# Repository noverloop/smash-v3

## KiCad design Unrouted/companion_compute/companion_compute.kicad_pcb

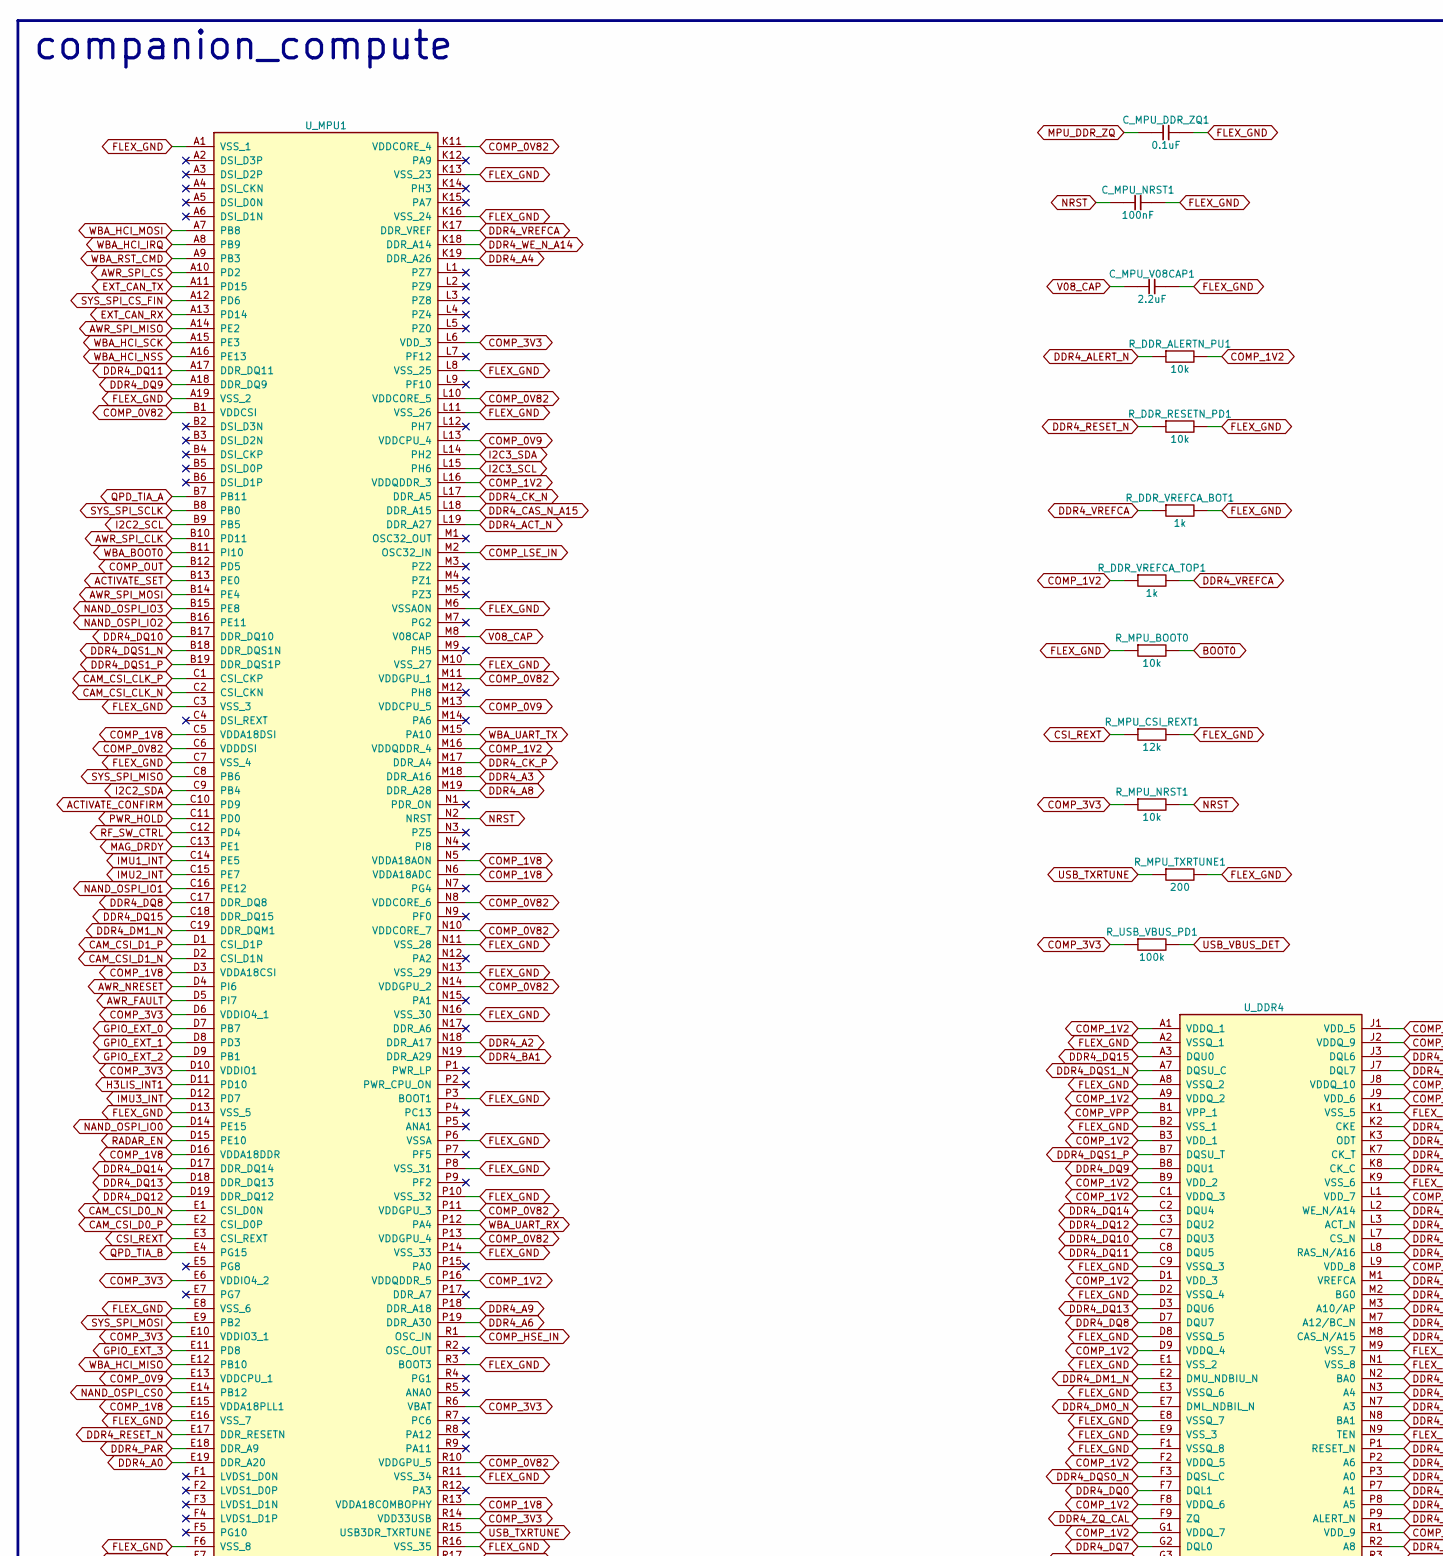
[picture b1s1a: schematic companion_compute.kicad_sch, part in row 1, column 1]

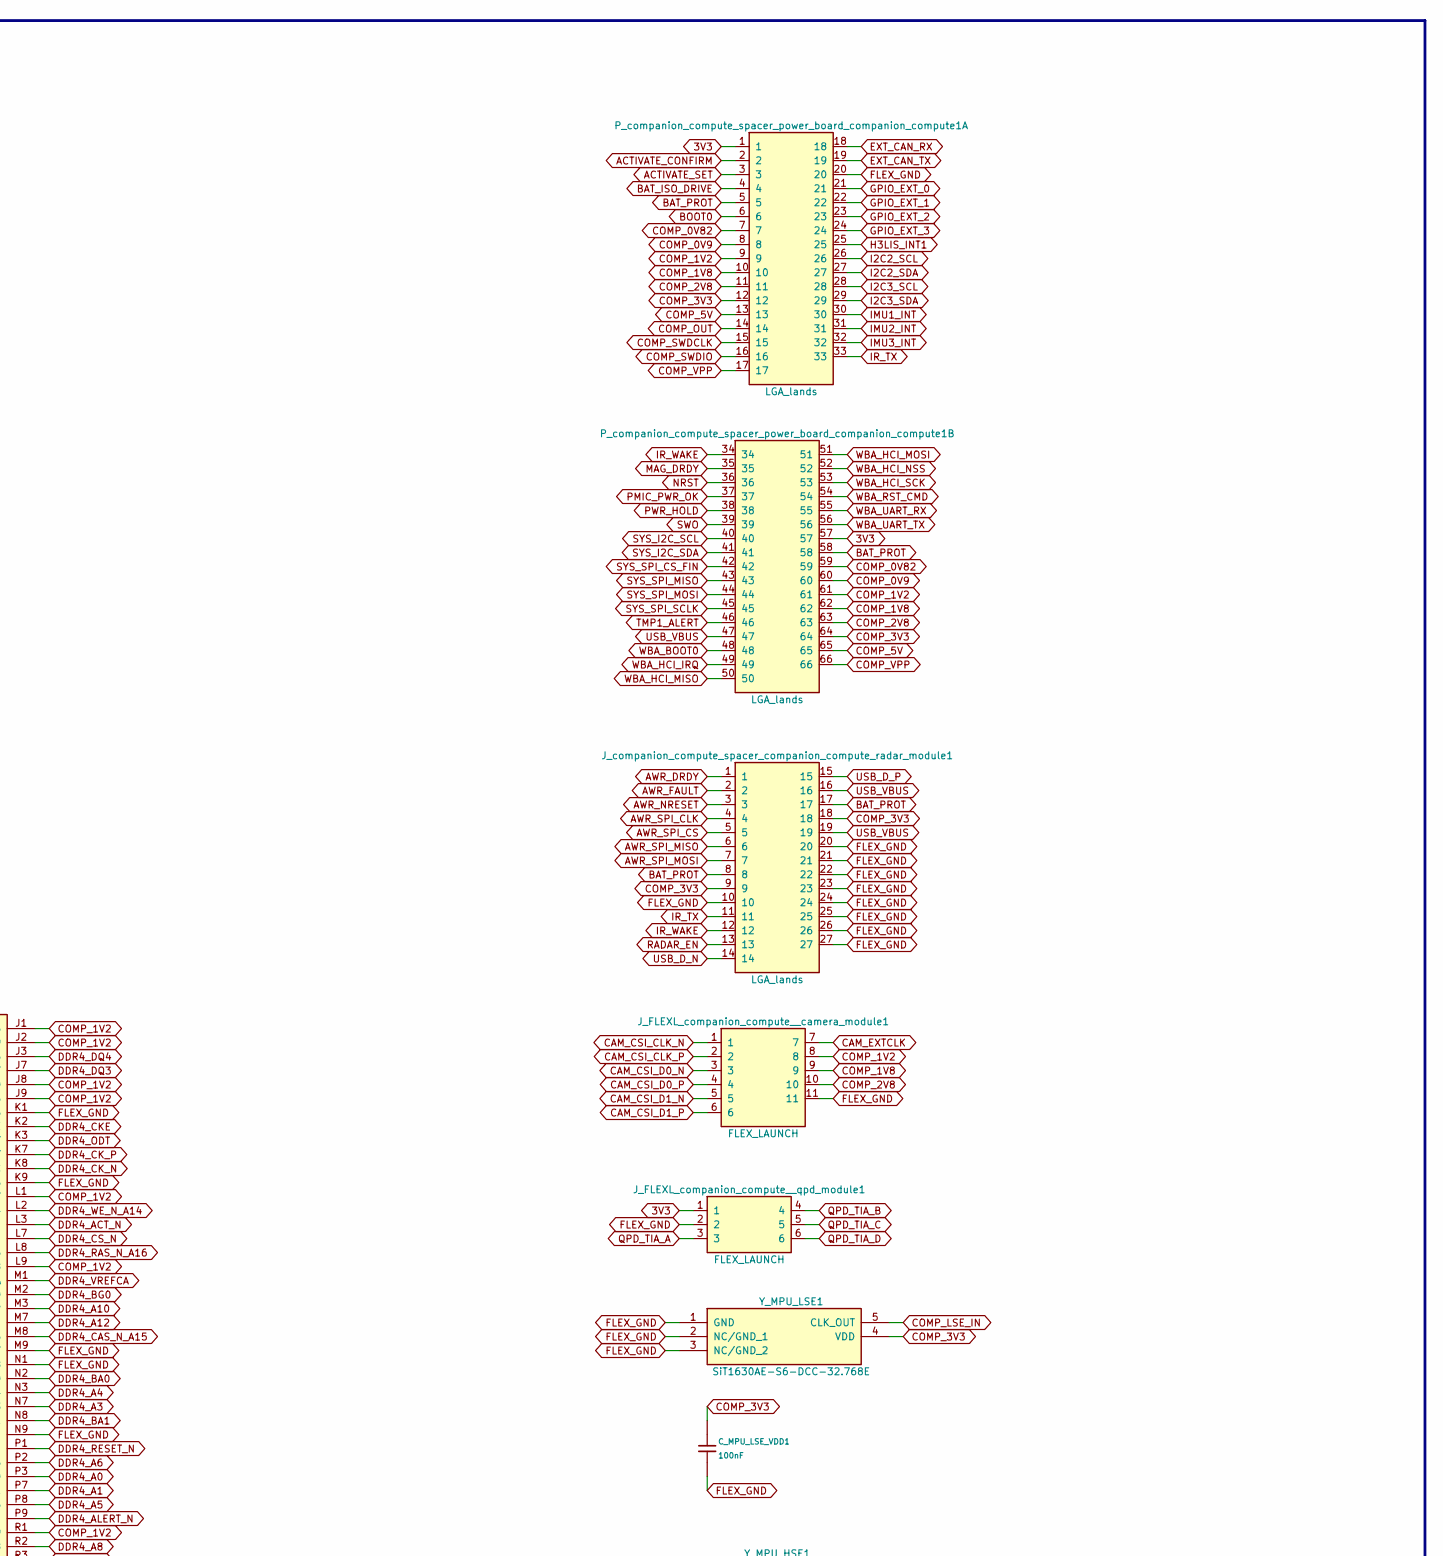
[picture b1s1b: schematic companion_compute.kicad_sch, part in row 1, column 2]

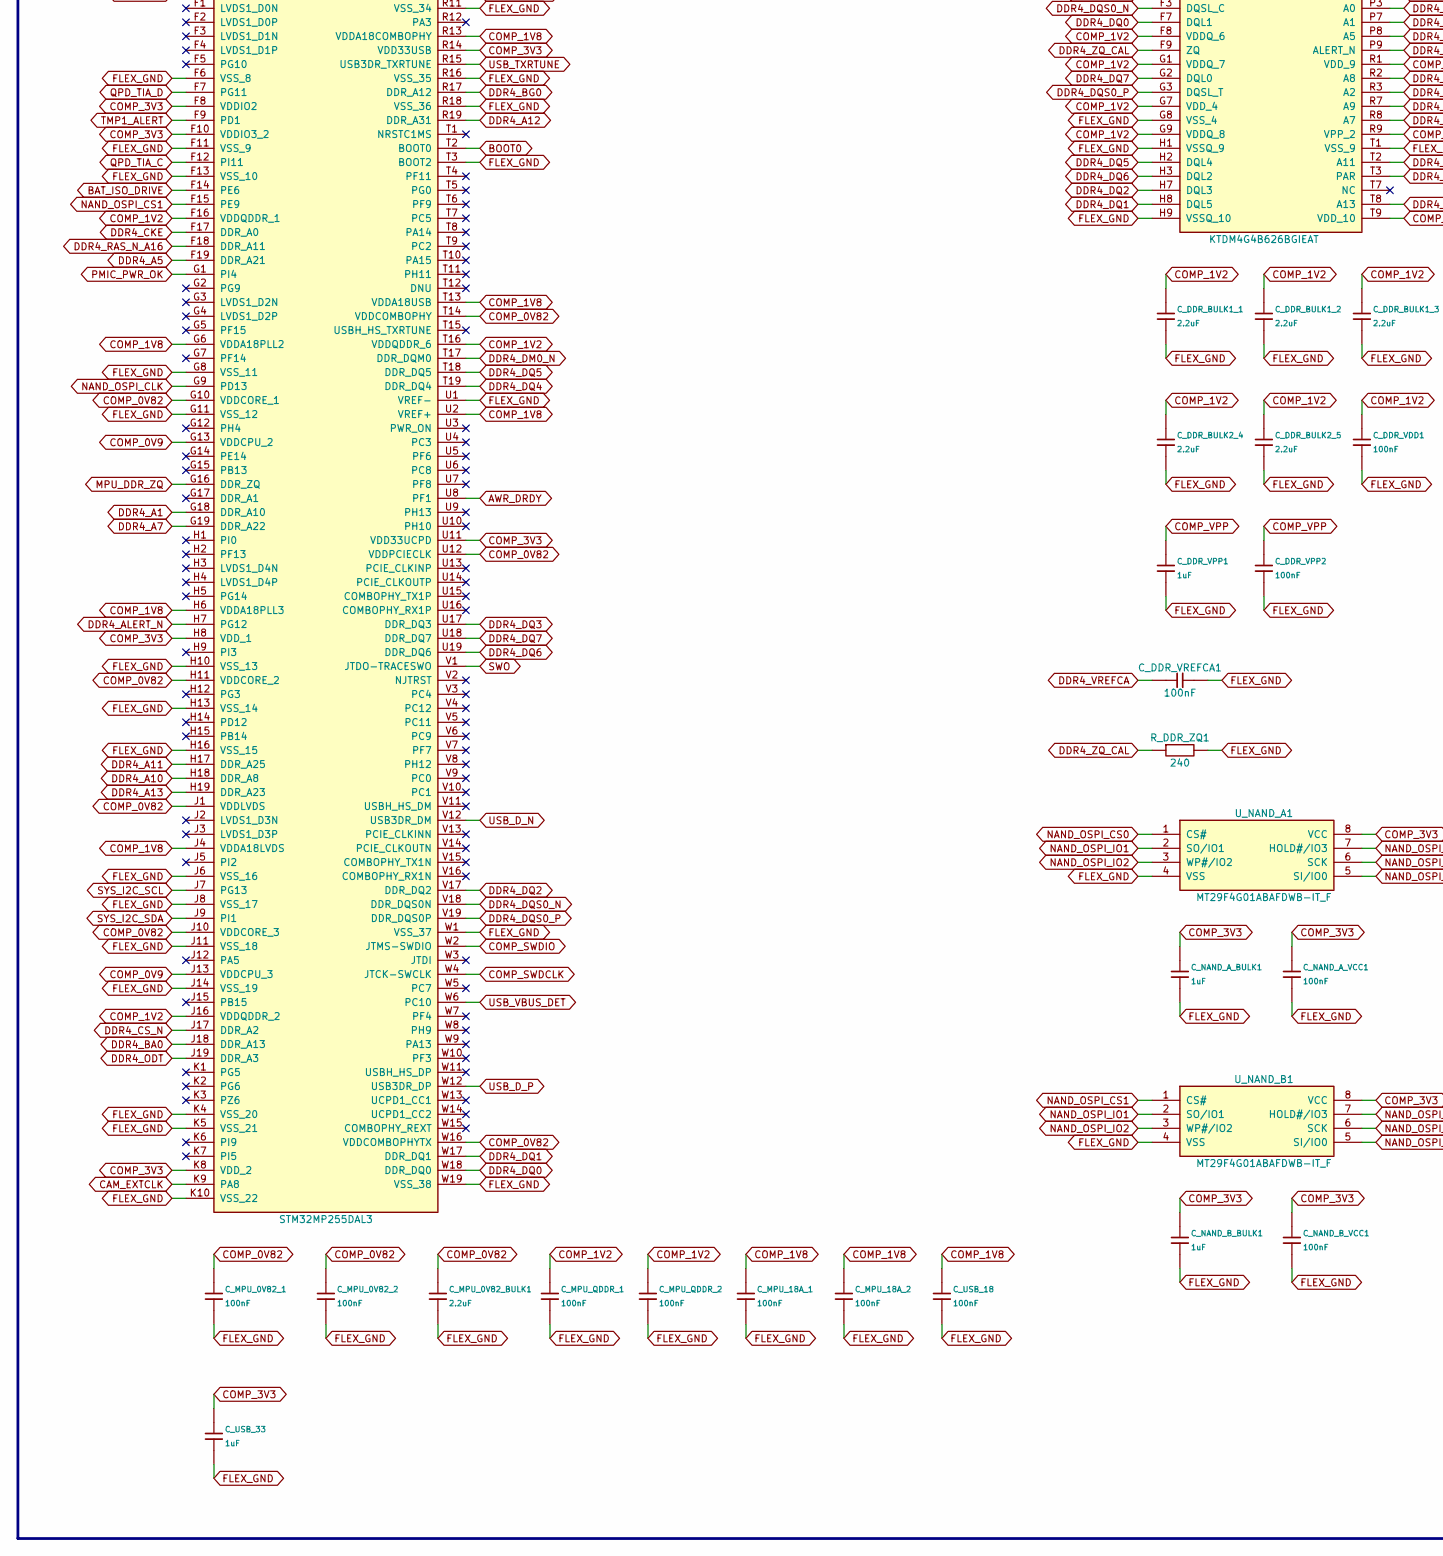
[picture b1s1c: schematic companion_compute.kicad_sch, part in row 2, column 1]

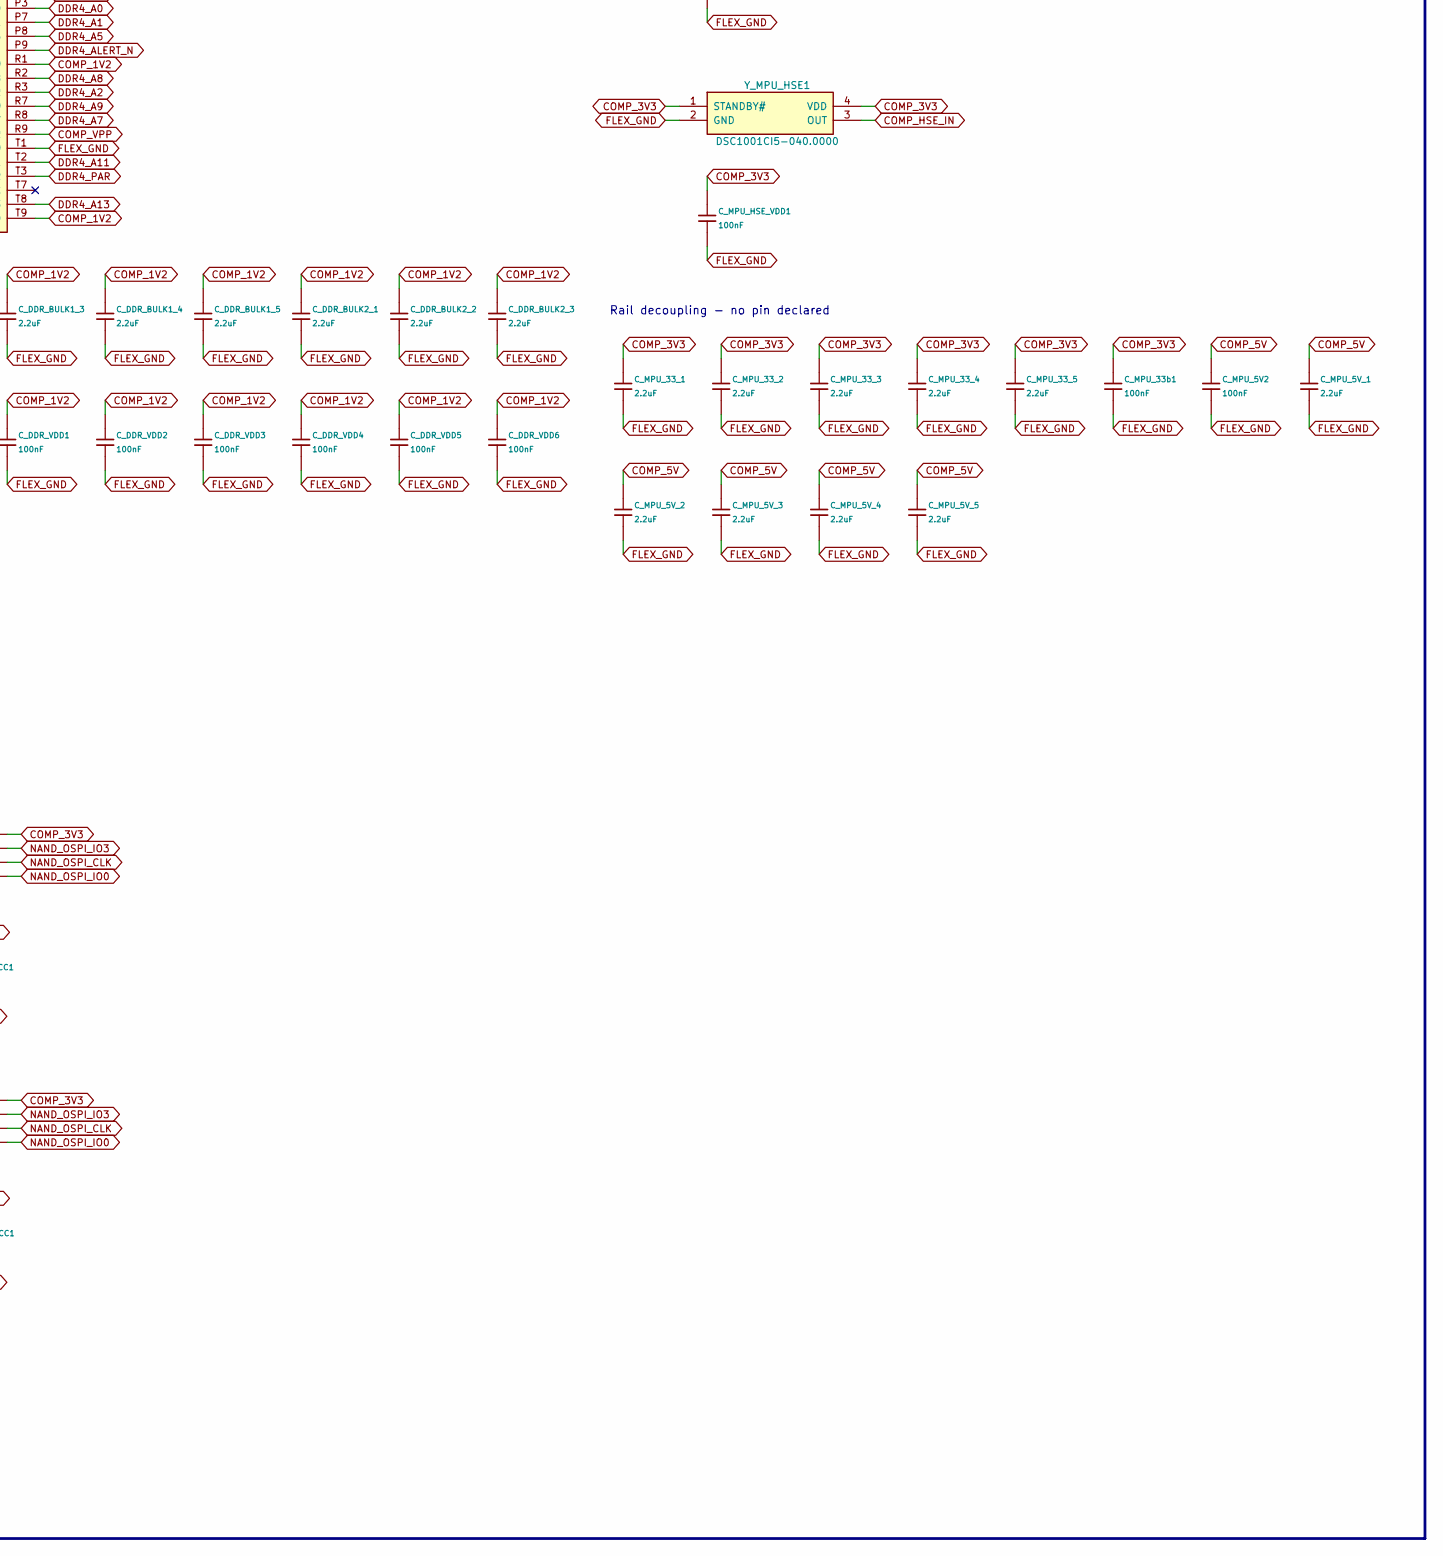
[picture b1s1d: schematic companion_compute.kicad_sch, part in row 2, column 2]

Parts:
C_DDR_BULK1_1, C_DDR_BULK1_2, C_DDR_BULK1_3, C_DDR_BULK1_4, C_DDR_BULK1_5, C_DDR_BULK2_1, C_DDR_BULK2_2, C_DDR_BULK2_3, C_DDR_BULK2_4, C_DDR_BULK2_5: 2.2uF; Capacitor_SMD_C_0603_1608Metric; MPN C-Series MIL-PRF-32535 X7R 0603 2.2uF
C_DDR_VDD1, C_DDR_VDD2, C_DDR_VDD3, C_DDR_VDD4, C_DDR_VDD5, C_DDR_VDD6: 100nF; Capacitor_SMD_C_0402_1005Metric; MPN C0402 X7R 100nF
C_DDR_VPP1: 1uF; Capacitor_SMD_C_0805_2012Metric; MPN C-Series MIL-PRF-32535 X7R 0805 1uF
C_DDR_VPP2: 100nF; Capacitor_SMD_C_0402_1005Metric; MPN C0402 X7R 100nF
C_DDR_VREFCA1: 100nF; Capacitor_SMD_C_0402_1005Metric; MPN C0402 X7R 100nF
C_MPU_0V82_1, C_MPU_0V82_2, C_MPU_5V2, C_MPU_18A_1, C_MPU_18A_2, C_MPU_33b1: 100nF; Capacitor_SMD_C_0402_1005Metric; MPN C0402 X7R 100nF
C_MPU_0V82_BULK1, C_MPU_5V_1, C_MPU_5V_2, C_MPU_5V_3, C_MPU_5V_4, C_MPU_5V_5, C_MPU_33_1, C_MPU_33_2, C_MPU_33_3, C_MPU_33_4, C_MPU_33_5: 2.2uF; Capacitor_SMD_C_0603_1608Metric; MPN C-Series MIL-PRF-32535 X7R 0603 2.2uF
C_MPU_DDR_ZQ1: 0.1uF; Capacitor_SMD_C_0402_1005Metric; MPN C0402 X7R 0.1uF
C_MPU_HSE_VDD1: 100nF; Capacitor_SMD_C_0402_1005Metric; MPN C0402 X7R 100nF
C_MPU_LSE_VDD1: 100nF; Capacitor_SMD_C_0402_1005Metric; MPN C0402 X7R 100nF
C_MPU_NRST1: 100nF; Capacitor_SMD_C_0402_1005Metric; MPN C0402 X7R 100nF
C_MPU_QDDR_1, C_MPU_QDDR_2: 100nF; Capacitor_SMD_C_0402_1005Metric; MPN C0402 X7R 100nF
C_MPU_V08CAP1: 2.2uF; Capacitor_SMD_C_0603_1608Metric; MPN C-Series MIL-PRF-32535 X7R 0603 2.2uF
C_NAND_A_BULK1: 1uF; Capacitor_SMD_C_0805_2012Metric; MPN C-Series MIL-PRF-32535 X7R 0805 1uF
C_NAND_A_VCC1: 100nF; Capacitor_SMD_C_0402_1005Metric; MPN C0402 X7R 100nF
C_NAND_B_BULK1: 1uF; Capacitor_SMD_C_0805_2012Metric; MPN C-Series MIL-PRF-32535 X7R 0805 1uF
C_NAND_B_VCC1: 100nF; Capacitor_SMD_C_0402_1005Metric; MPN C0402 X7R 100nF
C_USB_18: 100nF; Capacitor_SMD_C_0402_1005Metric; MPN C0402 X7R 100nF
C_USB_33: 1uF; Capacitor_SMD_C_0805_2012Metric; MPN C-Series MIL-PRF-32535 X7R 0805 1uF
J_FLEXL_companion_compute__camera_module1: FLEX_LAUNCH; J_FLEXL_companion_compute__camera_module; MPN FLEX_LAUNCH
J_FLEXL_companion_compute__qpd_module1: FLEX_LAUNCH; J_FLEXL_companion_compute__qpd_module; MPN FLEX_LAUNCH
J_companion_compute_spacer_companion_compute_radar_module1: LGA_lands; J_companion_compute_spacer_companion_compute_radar_module; MPN LGA_lands
P_companion_compute_spacer_power_board_companion_compute1: LGA_lands; P_companion_compute_spacer_power_board_companion_compute; MPN LGA_lands
R_DDR_ALERTN_PU1: 10k; Resistor_SMD_R_0402_1005Metric; MPN CRCW0402 10k 1% e3
R_DDR_RESETN_PD1: 10k; Resistor_SMD_R_0402_1005Metric; MPN CRCW0402 10k 1% e3
R_DDR_VREFCA_BOT1: 1k; Resistor_SMD_R_0402_1005Metric; MPN CRCW0402 1k 1% e3
R_DDR_VREFCA_TOP1: 1k; Resistor_SMD_R_0402_1005Metric; MPN CRCW0402 1k 1% e3
R_DDR_ZQ1: 240; Resistor_SMD_R_0402_1005Metric; MPN CRCW0402 240 1% e3
R_MPU_BOOT0: 10k; Resistor_SMD_R_0402_1005Metric; MPN CRCW0402 10k 1% e3
R_MPU_CSI_REXT1: 12k; Resistor_SMD_R_0402_1005Metric; MPN CRCW0402 12k 1% e3
R_MPU_NRST1: 10k; Resistor_SMD_R_0402_1005Metric; MPN CRCW0402 10k 1% e3
R_MPU_TXRTUNE1: 200; Resistor_SMD_R_0402_1005Metric; MPN CRCW0402 200 1% e3
R_USB_VBUS_PD1: 100k; Resistor_SMD_R_0402_1005Metric; MPN CRCW0402 100k 1% e3
U_DDR4: KTDM4G4B626BGIEAT; BGA96C80P9X16_750X1300X100; MPN KTDM4G4B626BGIEAT
U_MPU1: STM32MP255DAL3; MPN STM32MP255DAL3
U_NAND_A1: MT29F4G01ABAFDWB-IT_F; SON127P800X600X65-8N; MPN MT29F4G01ABAFDWB-IT_F
U_NAND_B1: MT29F4G01ABAFDWB-IT_F; SON127P800X600X65-8N; MPN MT29F4G01ABAFDWB-IT_F
Y_MPU_HSE1: DSC1001CI5-040.0000; DSC1001CI50080000; MPN DSC1001CI5-040.0000
Y_MPU_LSE1: SiT1630AE-S6-DCC-32.768E; SOT-23_5pins; MPN SiT1630AE-S6-DCC-32.768E

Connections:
3V3: J_FLEXL_companion_compute__qpd_module1.1, P_companion_compute_spacer_power_board_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.1, P_companion_compute_spacer_power_board_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.57
ACTIVATE_CONFIRM: P_companion_compute_spacer_power_board_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.2, U_MPU1.C10 (PD9)
ACTIVATE_SET: P_companion_compute_spacer_power_board_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.3, U_MPU1.B13 (PE0)
AWR_DRDY: J_companion_compute_spacer_companion_co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.1, U_MPU1.U8 (PF1)
AWR_FAULT: J_companion_compute_spacer_companion_co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.2, U_MPU1.D5 (PI7)
AWR_NRESET: J_companion_compute_spacer_companion_co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.3, U_MPU1.D4 (PI6)
AWR_SPI_CLK: J_companion_compute_spacer_companion_co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.4, U_MPU1.B10 (PD11)
AWR_SPI_CS: J_companion_compute_spacer_companion_co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.5, U_MPU1.A10 (PD2)
AWR_SPI_MISO: J_companion_compute_spacer_companion_co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.6, U_MPU1.A14 (PE2)
AWR_SPI_MOSI: J_companion_compute_spacer_companion_co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.7, U_MPU1.B14 (PE4)
BAT_ISO_DRIVE: P_companion_compute_spacer_power_board_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.4, U_MPU1.F14 (PE6)
BAT_PROT: J_companion_compute_spacer_companion_co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.8, J_companion_compute_spacer_companion_co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.17, P_companion_compute_spacer_power_board_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.5, P_companion_compute_spacer_power_board_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.58
BOOT0: P_companion_compute_spacer_power_board_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.6, R_MPU_BOOT0.2, U_MPU1.T2 (BOOT0)
CAM_CSI_CLK_N: J_FLEXL_companion_compute__camera_modul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.1, U_MPU1.C2 (CSI_CKN)
CAM_CSI_CLK_P: J_FLEXL_companion_compute__camera_modul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.2, U_MPU1.C1 (CSI_CKP)
CAM_CSI_D0_N: J_FLEXL_companion_compute__camera_modul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.3, U_MPU1.E1 (CSI_D0N)
CAM_CSI_D0_P: J_FLEXL_companion_compute__camera_modul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.4, U_MPU1.E2 (CSI_D0P)
CAM_CSI_D1_N: J_FLEXL_companion_compute__camera_modul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.5, U_MPU1.D2 (CSI_D1N)
CAM_CSI_D1_P: J_FLEXL_companion_compute__camera_modul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.6, U_MPU1.D1 (CSI_D1P)
CAM_EXTCLK: J_FLEXL_companion_compute__camera_modul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.7, U_MPU1.K9 (PA8)
COMP_0V9: P_companion_compute_spacer_power_board_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.8, P_companion_compute_spacer_power_board_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.60, U_MPU1.E13 (VDDCPU_1), U_MPU1.G13 (VDDCPU_2), U_MPU1.J13 (VDDCPU_3), U_MPU1.L13 (VDDCPU_4), U_MPU1.M13 (VDDCPU_5)
COMP_0V82: C_MPU_0V82_1.1, C_MPU_0V82_2.1, C_MPU_0V82_BULK1.1, P_companion_compute_spacer_power_board_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.7, P_companion_compute_spacer_power_board_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.59, U_MPU1.B1 (VDDCSI), U_MPU1.C6 (VDDDSI), U_MPU1.G10 (VDDCORE_1), U_MPU1.H11 (VDDCORE_2), U_MPU1.J1 (VDDLVDS), U_MPU1.J10 (VDDCORE_3), U_MPU1.K11 (VDDCORE_4), U_MPU1.L10 (VDDCORE_5), U_MPU1.M11 (VDDGPU_1), U_MPU1.N8 (VDDCORE_6), U_MPU1.N10 (VDDCORE_7), U_MPU1.N14 (VDDGPU_2), U_MPU1.P11 (VDDGPU_3), U_MPU1.P13 (VDDGPU_4), U_MPU1.R10 (VDDGPU_5), U_MPU1.T14 (VDDCOMBOPHY), U_MPU1.U12 (VDDPCIECLK), U_MPU1.W16 (VDDCOMBOPHYTX)
COMP_1V2: C_DDR_BULK1_1.1, C_DDR_BULK1_2.1, C_DDR_BULK1_3.1, C_DDR_BULK1_4.1, C_DDR_BULK1_5.1, C_DDR_BULK2_1.1, C_DDR_BULK2_2.1, C_DDR_BULK2_3.1, C_DDR_BULK2_4.1, C_DDR_BULK2_5.1, C_DDR_VDD1.1, C_DDR_VDD2.1, C_DDR_VDD3.1, C_DDR_VDD4.1, C_DDR_VDD5.1, C_DDR_VDD6.1, C_MPU_QDDR_1.1, C_MPU_QDDR_2.1, J_FLEXL_companion_compute__camera_modul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.8, P_companion_compute_spacer_power_board_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.9, P_companion_compute_spacer_power_board_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.61, R_DDR_ALERTN_PU1.2, R_DDR_VREFCA_TOP1.1, U_DDR4.A1 (VDDQ_1), U_DDR4.A9 (VDDQ_2), U_DDR4.B3 (VDD_1), U_DDR4.B9 (VDD_2), U_DDR4.C1 (VDDQ_3), U_DDR4.D1 (VDD_3), U_DDR4.D9 (VDDQ_4), U_DDR4.F2 (VDDQ_5), U_DDR4.F8 (VDDQ_6), U_DDR4.G1 (VDDQ_7), U_DDR4.G7 (VDD_4), U_DDR4.G9 (VDDQ_8), U_DDR4.J1 (VDD_5), U_DDR4.J2 (VDDQ_9), U_DDR4.J8 (VDDQ_10), U_DDR4.J9 (VDD_6), U_DDR4.L1 (VDD_7), U_DDR4.L9 (VDD_8), U_DDR4.R1 (VDD_9), U_DDR4.T9 (VDD_10), U_MPU1.F16 (VDDQDDR_1), U_MPU1.J16 (VDDQDDR_2), U_MPU1.L16 (VDDQDDR_3), U_MPU1.M16 (VDDQDDR_4), U_MPU1.P16 (VDDQDDR_5), U_MPU1.T16 (VDDQDDR_6)
COMP_1V8: C_MPU_18A_1.1, C_MPU_18A_2.1, C_USB_18.1, J_FLEXL_companion_compute__camera_modul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.9, P_companion_compute_spacer_power_board_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.10, P_companion_compute_spacer_power_board_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.62, U_MPU1.C5 (VDDA18DSI), U_MPU1.D3 (VDDA18CSI), U_MPU1.D16 (VDDA18DDR), U_MPU1.E15 (VDDA18PLL1), U_MPU1.G6 (VDDA18PLL2), U_MPU1.H6 (VDDA18PLL3), U_MPU1.J4 (VDDA18LVDS), U_MPU1.N5 (VDDA18AON), U_MPU1.N6 (VDDA18ADC), U_MPU1.R13 (VDDA18COMBOPHY), U_MPU1.T13 (VDDA18USB), U_MPU1.U2 (VREF+)
COMP_2V8: J_FLEXL_companion_compute__camera_modul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.10, P_companion_compute_spacer_power_board_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.11, P_companion_compute_spacer_power_board_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.63
COMP_3V3: C_MPU_33_1.1, C_MPU_33_2.1, C_MPU_33_3.1, C_MPU_33_4.1, C_MPU_33_5.1, C_MPU_33b1.1, C_MPU_HSE_VDD1.1, C_MPU_LSE_VDD1.1, C_NAND_A_BULK1.1, C_NAND_A_VCC1.1, C_NAND_B_BULK1.1, C_NAND_B_VCC1.1, C_USB_33.1, J_companion_compute_spacer_companion_co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.9, J_companion_compute_spacer_companion_co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.18, P_companion_compute_spacer_power_board_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.12, P_companion_compute_spacer_power_board_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.64, R_MPU_NRST1.1, R_USB_VBUS_PD1.1, U_MPU1.D6 (VDDIO4_1), U_MPU1.D10 (VDDIO1), U_MPU1.E6 (VDDIO4_2), U_MPU1.E10 (VDDIO3_1), U_MPU1.F8 (VDDIO2), U_MPU1.F10 (VDDIO3_2), U_MPU1.H8 (VDD_1), U_MPU1.K8 (VDD_2), U_MPU1.L6 (VDD_3), U_MPU1.R6 (VBAT), U_MPU1.R14 (VDD33USB), U_MPU1.U11 (VDD33UCPD), U_NAND_A1.8 (VCC), U_NAND_B1.8 (VCC), Y_MPU_HSE1.1 (STANDBY#), Y_MPU_HSE1.4 (VDD), Y_MPU_LSE1.4 (VDD)
COMP_5V: C_MPU_5V2.1, C_MPU_5V_1.1, C_MPU_5V_2.1, C_MPU_5V_3.1, C_MPU_5V_4.1, C_MPU_5V_5.1, P_companion_compute_spacer_power_board_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.13, P_companion_compute_spacer_power_board_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.65
COMP_HSE_IN: U_MPU1.R1 (OSC_IN), Y_MPU_HSE1.3 (OUT)
COMP_LSE_IN: U_MPU1.M2 (OSC32_IN), Y_MPU_LSE1.5 (CLK_OUT)
COMP_OUT: P_companion_compute_spacer_power_board_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.14, U_MPU1.B12 (PD5)
COMP_SWDCLK: P_companion_compute_spacer_power_board_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.15, U_MPU1.W4 (JTCK-SWCLK)
COMP_SWDIO: P_companion_compute_spacer_power_board_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.16, U_MPU1.W2 (JTMS-SWDIO)
COMP_VPP: C_DDR_VPP1.1, C_DDR_VPP2.1, P_companion_compute_spacer_power_board_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.17, P_companion_compute_spacer_power_board_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.66, U_DDR4.B1 (VPP_1), U_DDR4.R9 (VPP_2)
CSI_REXT: R_MPU_CSI_REXT1.1, U_MPU1.E3 (CSI_REXT)
DDR4_A0: U_DDR4.P3 (A0), U_MPU1.E19 (DDR_A20)
DDR4_A1: U_DDR4.P7 (A1), U_MPU1.G18 (DDR_A10)
DDR4_A2: U_DDR4.R3 (A2), U_MPU1.N18 (DDR_A17)
DDR4_A3: U_DDR4.N7 (A3), U_MPU1.M18 (DDR_A16)
DDR4_A4: U_DDR4.N3 (A4), U_MPU1.K19 (DDR_A26)
DDR4_A5: U_DDR4.P8 (A5), U_MPU1.F19 (DDR_A21)
DDR4_A6: U_DDR4.P2 (A6), U_MPU1.P19 (DDR_A30)
DDR4_A7: U_DDR4.R8 (A7), U_MPU1.G19 (DDR_A22)
DDR4_A8: U_DDR4.R2 (A8), U_MPU1.M19 (DDR_A28)
DDR4_A9: U_DDR4.R7 (A9), U_MPU1.P18 (DDR_A18)
DDR4_A10: U_DDR4.M3 (A10/AP), U_MPU1.H18 (DDR_A8)
DDR4_A11: U_DDR4.T2 (A11), U_MPU1.H17 (DDR_A25)
DDR4_A12: U_DDR4.M7 (A12/BC_N), U_MPU1.R19 (DDR_A31)
DDR4_A13: U_DDR4.T8 (A13), U_MPU1.H19 (DDR_A23)
DDR4_ACT_N: U_DDR4.L3 (ACT_N), U_MPU1.L19 (DDR_A27)
DDR4_ALERT_N: R_DDR_ALERTN_PU1.1, U_DDR4.P9 (ALERT_N), U_MPU1.H7 (PG12)
DDR4_BA0: U_DDR4.N2 (BA0), U_MPU1.J18 (DDR_A13)
DDR4_BA1: U_DDR4.N8 (BA1), U_MPU1.N19 (DDR_A29)
DDR4_BG0: U_DDR4.M2 (BG0), U_MPU1.R17 (DDR_A12)
DDR4_CAS_N_A15: U_DDR4.M8 (CAS_N/A15), U_MPU1.L18 (DDR_A15)
DDR4_CKE: U_DDR4.K2 (CKE), U_MPU1.F17 (DDR_A0)
DDR4_CK_N: U_DDR4.K8 (CK_C), U_MPU1.L17 (DDR_A5)
DDR4_CK_P: U_DDR4.K7 (CK_T), U_MPU1.M17 (DDR_A4)
DDR4_CS_N: U_DDR4.L7 (CS_N), U_MPU1.J17 (DDR_A2)
DDR4_DM0_N: U_DDR4.E7 (DML_NDBIL_N), U_MPU1.T17 (DDR_DQM0)
DDR4_DM1_N: U_DDR4.E2 (DMU_NDBIU_N), U_MPU1.C19 (DDR_DQM1)
DDR4_DQ0: U_DDR4.F7 (DQL1), U_MPU1.W18 (DDR_DQ0)
DDR4_DQ1: U_DDR4.H8 (DQL5), U_MPU1.W17 (DDR_DQ1)
DDR4_DQ2: U_DDR4.H7 (DQL3), U_MPU1.V17 (DDR_DQ2)
DDR4_DQ3: U_DDR4.J7 (DQL7), U_MPU1.U17 (DDR_DQ3)
DDR4_DQ4: U_DDR4.J3 (DQL6), U_MPU1.T19 (DDR_DQ4)
DDR4_DQ5: U_DDR4.H2 (DQL4), U_MPU1.T18 (DDR_DQ5)
DDR4_DQ6: U_DDR4.H3 (DQL2), U_MPU1.U19 (DDR_DQ6)
DDR4_DQ7: U_DDR4.G2 (DQL0), U_MPU1.U18 (DDR_DQ7)
DDR4_DQ8: U_DDR4.D7 (DQU7), U_MPU1.C17 (DDR_DQ8)
DDR4_DQ9: U_DDR4.B8 (DQU1), U_MPU1.A18 (DDR_DQ9)
DDR4_DQ10: U_DDR4.C7 (DQU3), U_MPU1.B17 (DDR_DQ10)
DDR4_DQ11: U_DDR4.C8 (DQU5), U_MPU1.A17 (DDR_DQ11)
DDR4_DQ12: U_DDR4.C3 (DQU2), U_MPU1.D19 (DDR_DQ12)
DDR4_DQ13: U_DDR4.D3 (DQU6), U_MPU1.D18 (DDR_DQ13)
DDR4_DQ14: U_DDR4.C2 (DQU4), U_MPU1.D17 (DDR_DQ14)
DDR4_DQ15: U_DDR4.A3 (DQU0), U_MPU1.C18 (DDR_DQ15)
DDR4_DQS0_N: U_DDR4.F3 (DQSL_C), U_MPU1.V18 (DDR_DQS0N)
DDR4_DQS0_P: U_DDR4.G3 (DQSL_T), U_MPU1.V19 (DDR_DQS0P)
DDR4_DQS1_N: U_DDR4.A7 (DQSU_C), U_MPU1.B18 (DDR_DQS1N)
DDR4_DQS1_P: U_DDR4.B7 (DQSU_T), U_MPU1.B19 (DDR_DQS1P)
DDR4_ODT: U_DDR4.K3 (ODT), U_MPU1.J19 (DDR_A3)
DDR4_PAR: U_DDR4.T3 (PAR), U_MPU1.E18 (DDR_A9)
DDR4_RAS_N_A16: U_DDR4.L8 (RAS_N/A16), U_MPU1.F18 (DDR_A11)
DDR4_RESET_N: R_DDR_RESETN_PD1.1, U_DDR4.P1 (RESET_N), U_MPU1.E17 (DDR_RESETN)
DDR4_VREFCA: C_DDR_VREFCA1.1, R_DDR_VREFCA_BOT1.1, R_DDR_VREFCA_TOP1.2, U_DDR4.M1 (VREFCA), U_MPU1.K17 (DDR_VREF)
DDR4_WE_N_A14: U_DDR4.L2 (WE_N/A14), U_MPU1.K18 (DDR_A14)
DDR4_ZQ_CAL: R_DDR_ZQ1.1, U_DDR4.F9 (ZQ)
EXT_CAN_RX: P_companion_compute_spacer_power_board_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.18, U_MPU1.A13 (PD14)
EXT_CAN_TX: P_companion_compute_spacer_power_board_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.19, U_MPU1.A11 (PD15)
FLEX_GND: C_DDR_BULK1_1.2, C_DDR_BULK1_2.2, C_DDR_BULK1_3.2, C_DDR_BULK1_4.2, C_DDR_BULK1_5.2, C_DDR_BULK2_1.2, C_DDR_BULK2_2.2, C_DDR_BULK2_3.2, C_DDR_BULK2_4.2, C_DDR_BULK2_5.2, C_DDR_VDD1.2, C_DDR_VDD2.2, C_DDR_VDD3.2, C_DDR_VDD4.2, C_DDR_VDD5.2, C_DDR_VDD6.2, C_DDR_VPP1.2, C_DDR_VPP2.2, C_DDR_VREFCA1.2, C_MPU_0V82_1.2, C_MPU_0V82_2.2, C_MPU_0V82_BULK1.2, C_MPU_5V2.2, C_MPU_5V_1.2, C_MPU_5V_2.2, C_MPU_5V_3.2, C_MPU_5V_4.2, C_MPU_5V_5.2, C_MPU_18A_1.2, C_MPU_18A_2.2, C_MPU_33_1.2, C_MPU_33_2.2, C_MPU_33_3.2, C_MPU_33_4.2, C_MPU_33_5.2, C_MPU_33b1.2, C_MPU_DDR_ZQ1.2, C_MPU_HSE_VDD1.2, C_MPU_LSE_VDD1.2, C_MPU_NRST1.2, C_MPU_QDDR_1.2, C_MPU_QDDR_2.2, C_MPU_V08CAP1.2, C_NAND_A_BULK1.2, C_NAND_A_VCC1.2, C_NAND_B_BULK1.2, C_NAND_B_VCC1.2, C_USB_18.2, C_USB_33.2, J_FLEXL_companion_compute__camera_modul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.11, J_FLEXL_companion_compute__qpd_module1.2, J_companion_compute_spacer_companion_co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.10, J_companion_compute_spacer_companion_co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.20, J_companion_compute_spacer_companion_co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.21, J_companion_compute_spacer_companion_co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.22, J_companion_compute_spacer_companion_co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.23, J_companion_compute_spacer_companion_co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.24, J_companion_compute_spacer_companion_co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.25, J_companion_compute_spacer_companion_co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.26, J_companion_compute_spacer_companion_co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.27, P_companion_compute_spacer_power_board_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.20, R_DDR_RESETN_PD1.2, R_DDR_VREFCA_BOT1.2, R_DDR_ZQ1.2, R_MPU_BOOT0.1, R_MPU_CSI_REXT1.2, R_MPU_TXRTUNE1.2, U_DDR4.A2 (VSSQ_1), U_DDR4.A8 (VSSQ_2), U_DDR4.B2 (VSS_1), U_DDR4.C9 (VSSQ_3), U_DDR4.D2 (VSSQ_4), U_DDR4.D8 (VSSQ_5), U_DDR4.E1 (VSS_2), U_DDR4.E3 (VSSQ_6), U_DDR4.E8 (VSSQ_7), U_DDR4.E9 (VSS_3), U_DDR4.F1 (VSSQ_8), U_DDR4.G8 (VSS_4), U_DDR4.H1 (VSSQ_9), U_DDR4.H9 (VSSQ_10), U_DDR4.K1 (VSS_5), U_DDR4.K9 (VSS_6), U_DDR4.M9 (VSS_7), U_DDR4.N1 (VSS_8), U_DDR4.N9 (TEN), U_DDR4.T1 (VSS_9), U_MPU1.A1 (VSS_1), U_MPU1.A19 (VSS_2), U_MPU1.C3 (VSS_3), U_MPU1.C7 (VSS_4), U_MPU1.D13 (VSS_5), U_MPU1.E8 (VSS_6), U_MPU1.E16 (VSS_7), U_MPU1.F6 (VSS_8), U_MPU1.F11 (VSS_9), U_MPU1.F13 (VSS_10), U_MPU1.G8 (VSS_11), U_MPU1.G11 (VSS_12), U_MPU1.H10 (VSS_13), U_MPU1.H13 (VSS_14), U_MPU1.H16 (VSS_15), U_MPU1.J6 (VSS_16), U_MPU1.J8 (VSS_17), U_MPU1.J11 (VSS_18), U_MPU1.J14 (VSS_19), U_MPU1.K4 (VSS_20), U_MPU1.K5 (VSS_21), U_MPU1.K10 (VSS_22), U_MPU1.K13 (VSS_23), U_MPU1.K16 (VSS_24), U_MPU1.L8 (VSS_25), U_MPU1.L11 (VSS_26), U_MPU1.M6 (VSSAON), U_MPU1.M10 (VSS_27), U_MPU1.N11 (VSS_28), U_MPU1.N13 (VSS_29), U_MPU1.N16 (VSS_30), U_MPU1.P3 (BOOT1), U_MPU1.P6 (VSSA), U_MPU1.P8 (VSS_31), U_MPU1.P10 (VSS_32), U_MPU1.P14 (VSS_33), U_MPU1.R3 (BOOT3), U_MPU1.R11 (VSS_34), U_MPU1.R16 (VSS_35), U_MPU1.R18 (VSS_36), U_MPU1.T3 (BOOT2), U_MPU1.U1 (VREF-), U_MPU1.W1 (VSS_37), U_MPU1.W19 (VSS_38), U_NAND_A1.4 (VSS), U_NAND_B1.4 (VSS), Y_MPU_HSE1.2 (GND), Y_MPU_LSE1.1 (GND), Y_MPU_LSE1.2 (NC/GND_1), Y_MPU_LSE1.3 (NC/GND_2)
GPIO_EXT_0: P_companion_compute_spacer_power_board_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.21, U_MPU1.D7 (PB7)
GPIO_EXT_1: P_companion_compute_spacer_power_board_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.22, U_MPU1.D8 (PD3)
GPIO_EXT_2: P_companion_compute_spacer_power_board_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.23, U_MPU1.D9 (PB1)
GPIO_EXT_3: P_companion_compute_spacer_power_board_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.24, U_MPU1.E11 (PD8)
H3LIS_INT1: P_companion_compute_spacer_power_board_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.25, U_MPU1.D11 (PD10)
I2C2_SCL: P_companion_compute_spacer_power_board_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.26, U_MPU1.B9 (PB5)
I2C2_SDA: P_companion_compute_spacer_power_board_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.27, U_MPU1.C9 (PB4)
I2C3_SCL: P_companion_compute_spacer_power_board_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.28, U_MPU1.L15 (PH6)
I2C3_SDA: P_companion_compute_spacer_power_board_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.29, U_MPU1.L14 (PH2)
IMU1_INT: P_companion_compute_spacer_power_board_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.30, U_MPU1.C14 (PE5)
IMU2_INT: P_companion_compute_spacer_power_board_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.31, U_MPU1.C15 (PE7)
IMU3_INT: P_companion_compute_spacer_power_board_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.32, U_MPU1.D12 (PD7)
IR_TX: J_companion_compute_spacer_companion_co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.11, P_companion_compute_spacer_power_board_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.33
IR_WAKE: J_companion_compute_spacer_companion_co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.12, P_companion_compute_spacer_power_board_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.34
MAG_DRDY: P_companion_compute_spacer_power_board_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.35, U_MPU1.C13 (PE1)
MPU_DDR_ZQ: C_MPU_DDR_ZQ1.1, U_MPU1.G16 (DDR_ZQ)
NAND_OSPI_CLK: U_MPU1.G9 (PD13), U_NAND_A1.6 (SCK), U_NAND_B1.6 (SCK)
NAND_OSPI_CS0: U_MPU1.E14 (PB12), U_NAND_A1.1 (CS#)
NAND_OSPI_CS1: U_MPU1.F15 (PE9), U_NAND_B1.1 (CS#)
NAND_OSPI_IO0: U_MPU1.D14 (PE15), U_NAND_A1.5 (SI/IO0), U_NAND_B1.5 (SI/IO0)
NAND_OSPI_IO1: U_MPU1.C16 (PE12), U_NAND_A1.2 (SO/IO1), U_NAND_B1.2 (SO/IO1)
NAND_OSPI_IO2: U_MPU1.B16 (PE11), U_NAND_A1.3 (WP#/IO2), U_NAND_B1.3 (WP#/IO2)
NAND_OSPI_IO3: U_MPU1.B15 (PE8), U_NAND_A1.7 (HOLD#/IO3), U_NAND_B1.7 (HOLD#/IO3)
NRST: C_MPU_NRST1.1, P_companion_compute_spacer_power_board_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.36, R_MPU_NRST1.2, U_MPU1.N2 (NRST)
PMIC_PWR_OK: P_companion_compute_spacer_power_board_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.37, U_MPU1.G1 (PI4)
PWR_HOLD: P_companion_compute_spacer_power_board_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.38, U_MPU1.C11 (PD0)
QPD_TIA_A: J_FLEXL_companion_compute__qpd_module1.3, U_MPU1.B7 (PB11)
QPD_TIA_B: J_FLEXL_companion_compute__qpd_module1.4, U_MPU1.E4 (PG15)
QPD_TIA_C: J_FLEXL_companion_compute__qpd_module1.5, U_MPU1.F12 (PI11)
QPD_TIA_D: J_FLEXL_companion_compute__qpd_module1.6, U_MPU1.F7 (PG11)
RADAR_EN: J_companion_compute_spacer_companion_co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.13, U_MPU1.D15 (PE10)
RF_SW_CTRL: U_MPU1.C12 (PD4)
SWO: P_companion_compute_spacer_power_board_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.39, U_MPU1.V1 (JTDO-TRACESWO)
SYS_I2C_SCL: P_companion_compute_spacer_power_board_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.40, U_MPU1.J7 (PG13)
SYS_I2C_SDA: P_companion_compute_spacer_power_board_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.41, U_MPU1.J9 (PI1)
SYS_SPI_CS_FIN: P_companion_compute_spacer_power_board_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.42, U_MPU1.A12 (PD6)
SYS_SPI_MISO: P_companion_compute_spacer_power_board_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.43, U_MPU1.C8 (PB6)
SYS_SPI_MOSI: P_companion_compute_spacer_power_board_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.44, U_MPU1.E9 (PB2)
SYS_SPI_SCLK: P_companion_compute_spacer_power_board_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.45, U_MPU1.B8 (PB0)
TMP1_ALERT: P_companion_compute_spacer_power_board_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.46, U_MPU1.F9 (PD1)
USB_D_N: J_companion_compute_spacer_companion_co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.14, U_MPU1.V12 (USB3DR_DM)
USB_D_P: J_companion_compute_spacer_companion_co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.15, U_MPU1.W12 (USB3DR_DP)
USB_TXRTUNE: R_MPU_TXRTUNE1.1, U_MPU1.R15 (USB3DR_TXRTUNE)
USB_VBUS: J_companion_compute_spacer_companion_co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.16, J_companion_compute_spacer_companion_co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.19, P_companion_compute_spacer_power_board_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.47
USB_VBUS_DET: R_USB_VBUS_PD1.2, U_MPU1.W6 (PC10)
V08_CAP: C_MPU_V08CAP1.1, U_MPU1.M8 (V08CAP)
WBA_BOOT0: P_companion_compute_spacer_power_board_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.48, U_MPU1.B11 (PI10)
WBA_HCI_IRQ: P_companion_compute_spacer_power_board_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.49, U_MPU1.A8 (PB9)
WBA_HCI_MISO: P_companion_compute_spacer_power_board_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.50, U_MPU1.E12 (PB10)
WBA_HCI_MOSI: P_companion_compute_spacer_power_board_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.51, U_MPU1.A7 (PB8)
WBA_HCI_NSS: P_companion_compute_spacer_power_board_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.52, U_MPU1.A16 (PE13)
WBA_HCI_SCK: P_companion_compute_spacer_power_board_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.53, U_MPU1.A15 (PE3)
WBA_RST_CMD: P_companion_compute_spacer_power_board_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.54, U_MPU1.A9 (PB3)
WBA_UART_RX: P_companion_compute_spacer_power_board_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.55, U_MPU1.P12 (PA4)
WBA_UART_TX: P_companion_compute_spacer_power_board_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.56, U_MPU1.M15 (PA10)

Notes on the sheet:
companion_compute
Rail decoupling - no pin declared

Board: 20 copper layers, 71 parts (62 on the bottom side), 144 nets, no tracks yet.

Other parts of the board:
MH1, MH2: smash_mech_potting
